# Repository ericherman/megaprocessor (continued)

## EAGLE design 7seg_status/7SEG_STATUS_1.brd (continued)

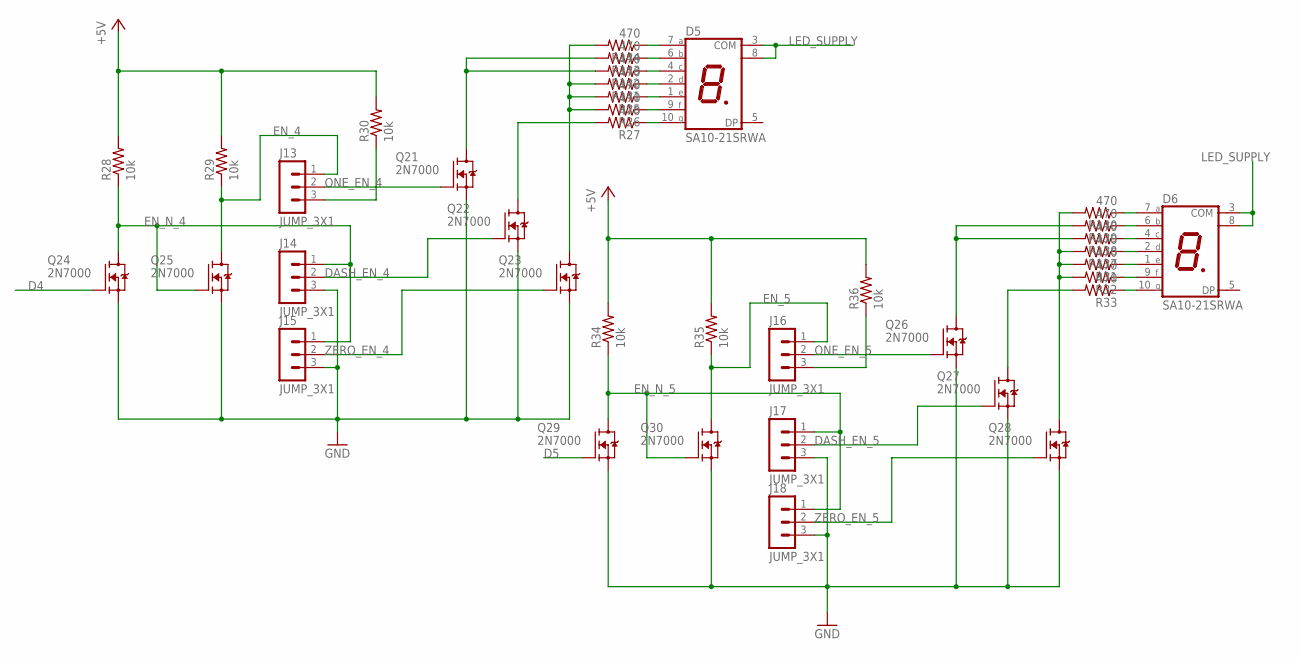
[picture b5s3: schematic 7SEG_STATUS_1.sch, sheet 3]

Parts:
D5, D6: SA10-21SRWA; SA10
J13, J14, J15, J16, J17, J18: JUMP_3X1
Q21, Q22, Q23, Q24, Q25, Q26, Q27, Q28, Q29, Q30: 2N7000; TO92-DGS
R25, R26, R27, R31, R32, R33, R137, R138, R139, R140, R141, R142, R143, R144: 470; R_P2INCH
R28, R29, R30, R34, R35, R36: 10k; R_P2INCH

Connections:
+5V: R28.2, R29.2, R30.2, R34.2, R35.2, R36.2; also elsewhere on the board
D4: Q24.G; also elsewhere on the board
D5: Q29.G; also elsewhere on the board
DASH_EN_4: J14.2, Q22.G
DASH_EN_5: J17.2, Q27.G
EN_4: J13.1, Q25.D, R29.1
EN_5: J16.1, Q30.D, R35.1
EN_N_4: J14.1, J15.1, Q24.D, Q25.G, R28.1
EN_N_5: J17.1, J18.1, Q29.D, Q30.G, R34.1
GND: J14.3, J15.3, J17.3, J18.3, Q21.S, Q22.S, Q23.S, Q24.S, Q25.S, Q26.S, Q27.S, Q28.S, Q29.S, Q30.S; also elsewhere on the board
LED_SUPPLY: D5.3 (COM), D5.8 (COM), D6.3 (COM), D6.8 (COM); also elsewhere on the board
unnamed: Q22.D, R27.2
unnamed: D6.7 (A), R140.1
unnamed: D6.6 (B), R139.1
unnamed: D6.4 (C), R138.1
unnamed: J13.3, R30.1
unnamed: D6.2 (D), R137.1
unnamed: D6.1 (E), R31.1
unnamed: D6.9 (F), R32.1
unnamed: Q21.D, R142.2, R143.2
unnamed: J16.3, R36.1
unnamed: D6.10 (G), R33.1
unnamed: Q26.D, R138.2, R139.2
unnamed: Q27.D, R33.2
unnamed: Q28.D, R31.2, R32.2, R137.2, R140.2
unnamed: Q23.D, R25.2, R26.2, R141.2, R144.2
unnamed: D5.7 (A), R144.1
unnamed: D5.6 (B), R143.1
unnamed: D5.4 (C), R142.1
unnamed: D5.2 (D), R141.1
unnamed: D5.1 (E), R25.1
unnamed: D5.9 (F), R26.1
unnamed: D5.10 (G), R27.1
ONE_EN_4: J13.2, Q21.G
ONE_EN_5: J16.2, Q26.G
ZERO_EN_4: J15.2, Q23.G
ZERO_EN_5: J18.2, Q28.G

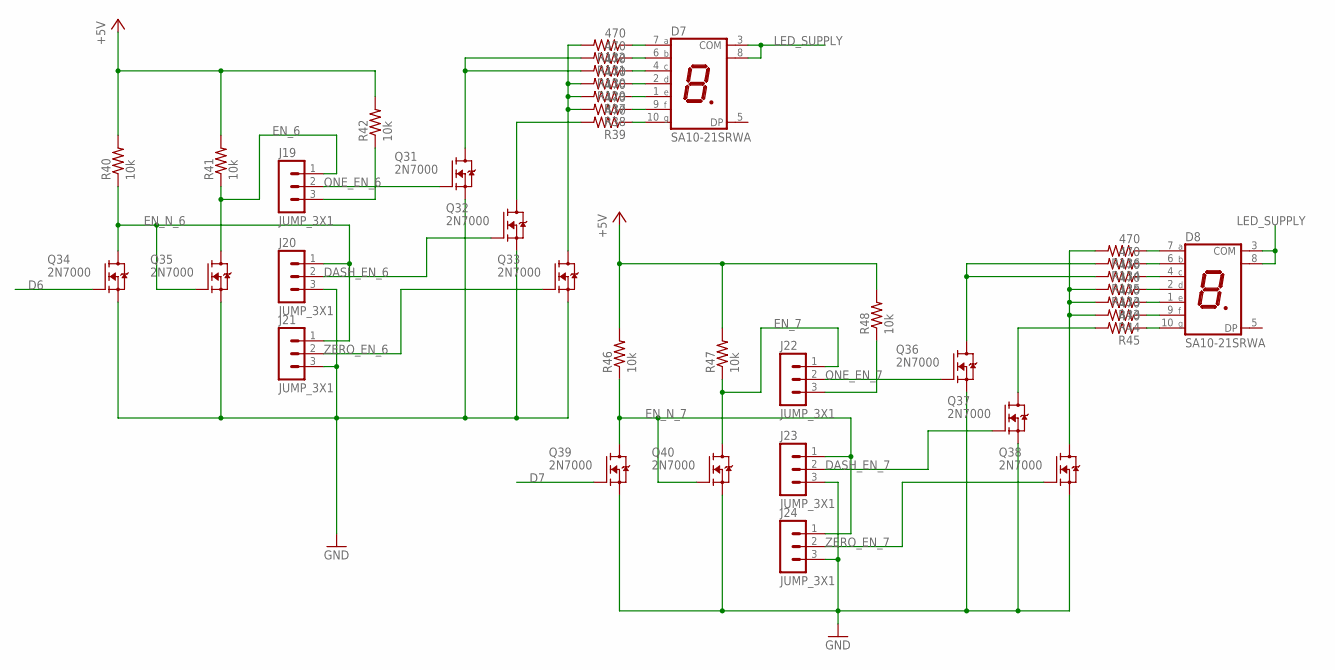
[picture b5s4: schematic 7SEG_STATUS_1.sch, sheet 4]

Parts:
D7, D8: SA10-21SRWA; SA10
J19, J20, J21, J22, J23, J24: JUMP_3X1
Q31, Q32, Q33, Q34, Q35, Q36, Q37, Q38, Q39, Q40: 2N7000; TO92-DGS
R37, R38, R39, R43, R44, R45, R129, R130, R131, R132, R133, R134, R135, R136: 470; R_P2INCH
R40, R41, R42, R46, R47, R48: 10k; R_P2INCH

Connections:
+5V: R40.2, R41.2, R42.2, R46.2, R47.2, R48.2; also elsewhere on the board
D6: Q34.G; also elsewhere on the board
D7: Q39.G; also elsewhere on the board
DASH_EN_6: J20.2, Q32.G
DASH_EN_7: J23.2, Q37.G
EN_6: J19.1, Q35.D, R41.1
EN_7: J22.1, Q40.D, R47.1
EN_N_6: J20.1, J21.1, Q34.D, Q35.G, R40.1
EN_N_7: J23.1, J24.1, Q39.D, Q40.G, R46.1
GND: J20.3, J21.3, J23.3, J24.3, Q31.S, Q32.S, Q33.S, Q34.S, Q35.S, Q36.S, Q37.S, Q38.S, Q39.S, Q40.S; also elsewhere on the board
LED_SUPPLY: D7.3 (COM), D7.8 (COM), D8.3 (COM), D8.8 (COM); also elsewhere on the board
unnamed: D7.7 (A), R132.1
unnamed: D7.6 (B), R131.1
unnamed: D7.4 (C), R130.1
unnamed: D7.2 (D), R129.1
unnamed: J19.3, R42.1
unnamed: D7.1 (E), R37.1
unnamed: D7.9 (F), R38.1
unnamed: D7.10 (G), R39.1
unnamed: D8.7 (A), R136.1
unnamed: J22.3, R48.1
unnamed: Q32.D, R39.2
unnamed: Q31.D, R130.2, R131.2
unnamed: D8.6 (B), R134.1
unnamed: D8.4 (C), R135.1
unnamed: D8.2 (D), R133.1
unnamed: D8.1 (E), R43.1
unnamed: D8.9 (F), R44.1
unnamed: D8.10 (G), R45.1
unnamed: Q37.D, R45.2
unnamed: Q36.D, R134.2, R135.2
unnamed: Q38.D, R43.2, R44.2, R133.2, R136.2
unnamed: Q33.D, R37.2, R38.2, R129.2, R132.2
ONE_EN_6: J19.2, Q31.G
ONE_EN_7: J22.2, Q36.G
ZERO_EN_6: J21.2, Q33.G
ZERO_EN_7: J24.2, Q38.G

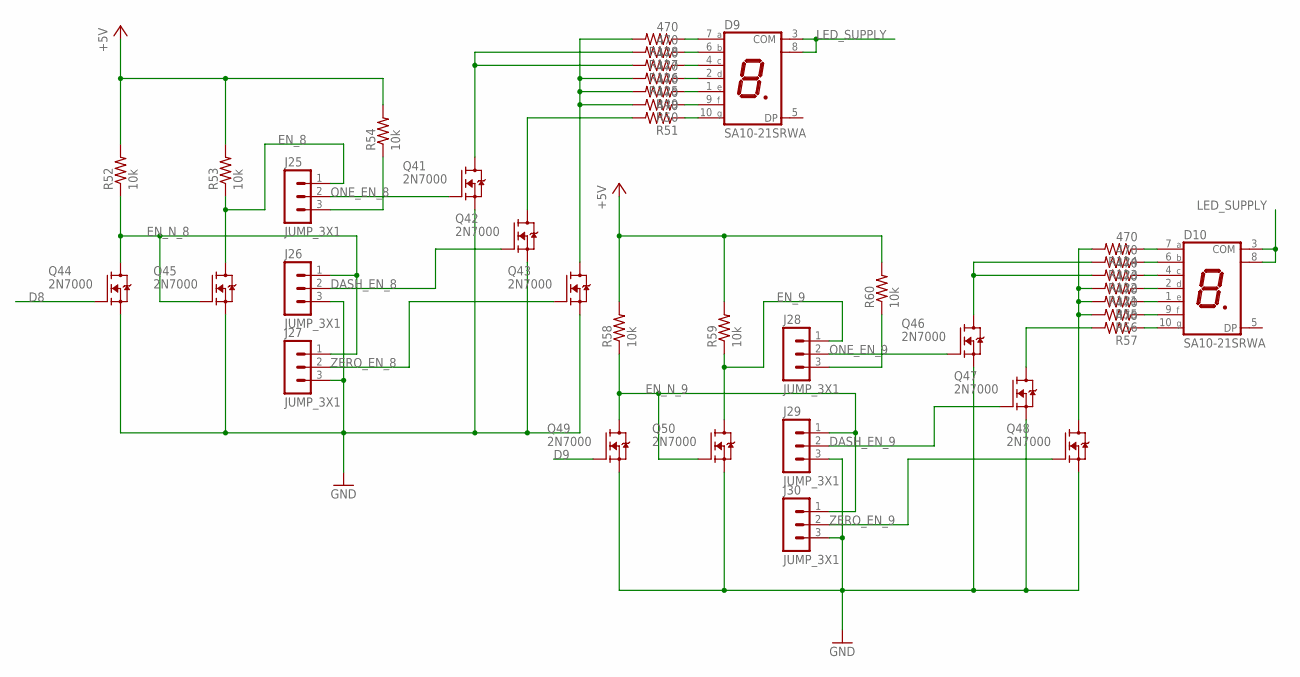
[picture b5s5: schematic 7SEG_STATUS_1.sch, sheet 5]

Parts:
D9, D10: SA10-21SRWA; SA10
J25, J26, J27, J28, J29, J30: JUMP_3X1
Q41, Q42, Q43, Q44, Q45, Q46, Q47, Q48, Q49, Q50: 2N7000; TO92-DGS
R49, R50, R51, R55, R56, R57, R121, R122, R123, R124, R125, R126, R127, R128: 470; R_P2INCH
R52, R53, R54, R58, R59, R60: 10k; R_P2INCH

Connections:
+5V: R52.2, R53.2, R54.2, R58.2, R59.2, R60.2; also elsewhere on the board
D8: Q44.G; also elsewhere on the board
D9: Q49.G; also elsewhere on the board
DASH_EN_8: J26.2, Q42.G
DASH_EN_9: J29.2, Q47.G
EN_8: J25.1, Q45.D, R53.1
EN_9: J28.1, Q50.D, R59.1
EN_N_8: J26.1, J27.1, Q44.D, Q45.G, R52.1
EN_N_9: J29.1, J30.1, Q49.D, Q50.G, R58.1
GND: J26.3, J27.3, J29.3, J30.3, Q41.S, Q42.S, Q43.S, Q44.S, Q45.S, Q46.S, Q47.S, Q48.S, Q49.S, Q50.S; also elsewhere on the board
LED_SUPPLY: D9.3 (COM), D9.8 (COM), D10.3 (COM), D10.8 (COM); also elsewhere on the board
unnamed: D9.7 (A), R128.1
unnamed: D10.10 (G), R57.1
unnamed: D10.9 (F), R56.1
unnamed: J25.3, R54.1
unnamed: D10.1 (E), R55.1
unnamed: D10.2 (D), R121.1
unnamed: D10.4 (C), R122.1
unnamed: D10.6 (B), R123.1
unnamed: J28.3, R60.1
unnamed: D10.7 (A), R124.1
unnamed: Q47.D, R57.2
unnamed: Q46.D, R122.2, R123.2
unnamed: Q48.D, R55.2, R56.2, R121.2, R124.2
unnamed: D9.6 (B), R127.1
unnamed: D9.4 (C), R126.1
unnamed: D9.2 (D), R125.1
unnamed: D9.1 (E), R49.1
unnamed: D9.9 (F), R50.1
unnamed: D9.10 (G), R51.1
unnamed: Q42.D, R51.2
unnamed: Q41.D, R126.2, R127.2
unnamed: Q43.D, R49.2, R50.2, R125.2, R128.2
ONE_EN_8: J25.2, Q41.G
ONE_EN_9: J28.2, Q46.G
ZERO_EN_8: J27.2, Q43.G
ZERO_EN_9: J30.2, Q48.G

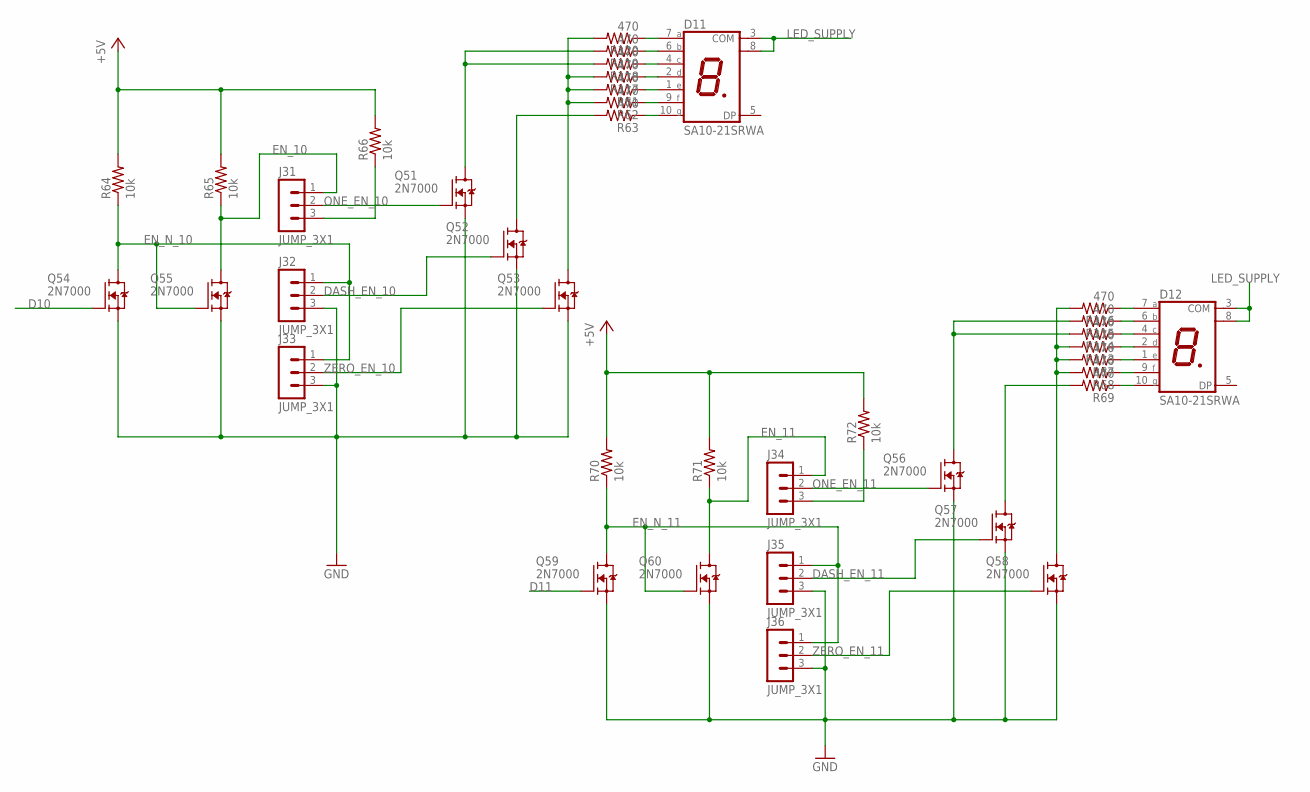
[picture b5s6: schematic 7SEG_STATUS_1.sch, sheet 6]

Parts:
D11, D12: SA10-21SRWA; SA10
J31, J32, J33, J34, J35, J36: JUMP_3X1
Q51, Q52, Q53, Q54, Q55, Q56, Q57, Q58, Q59, Q60: 2N7000; TO92-DGS
R61, R62, R63, R67, R68, R69, R113, R114, R115, R116, R117, R118, R119, R120: 470; R_P2INCH
R64, R65, R66, R70, R71, R72: 10k; R_P2INCH

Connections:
+5V: R64.2, R65.2, R66.2, R70.2, R71.2, R72.2; also elsewhere on the board
D10: Q54.G; also elsewhere on the board
D11: Q59.G; also elsewhere on the board
DASH_EN_10: J32.2, Q52.G
DASH_EN_11: J35.2, Q57.G
EN_10: J31.1, Q55.D, R65.1
EN_11: J34.1, Q60.D, R71.1
EN_N_10: J32.1, J33.1, Q54.D, Q55.G, R64.1
EN_N_11: J35.1, J36.1, Q59.D, Q60.G, R70.1
GND: J32.3, J33.3, J35.3, J36.3, Q51.S, Q52.S, Q53.S, Q54.S, Q55.S, Q56.S, Q57.S, Q58.S, Q59.S, Q60.S; also elsewhere on the board
LED_SUPPLY: D11.3 (COM), D11.8 (COM), D12.3 (COM), D12.8 (COM); also elsewhere on the board
unnamed: Q52.D, R63.2
unnamed: Q51.D, R118.2, R119.2
unnamed: D11.6 (B), R119.1
unnamed: D12.7 (A), R116.1
unnamed: J31.3, R66.1
unnamed: D12.6 (B), R115.1
unnamed: D12.4 (C), R114.1
unnamed: D12.2 (D), R113.1
unnamed: D11.4 (C), R118.1
unnamed: J34.3, R72.1
unnamed: D12.1 (E), R67.1
unnamed: D12.9 (F), R68.1
unnamed: D12.10 (G), R69.1
unnamed: Q58.D, R67.2, R68.2, R113.2, R116.2
unnamed: Q56.D, R114.2, R115.2
unnamed: Q57.D, R69.2
unnamed: D11.2 (D), R117.1
unnamed: D11.1 (E), R61.1
unnamed: D11.9 (F), R62.1
unnamed: D11.10 (G), R63.1
unnamed: D11.7 (A), R120.1
unnamed: Q53.D, R61.2, R62.2, R117.2, R120.2
ONE_EN_10: J31.2, Q51.G
ONE_EN_11: J34.2, Q56.G
ZERO_EN_10: J33.2, Q53.G
ZERO_EN_11: J36.2, Q58.G

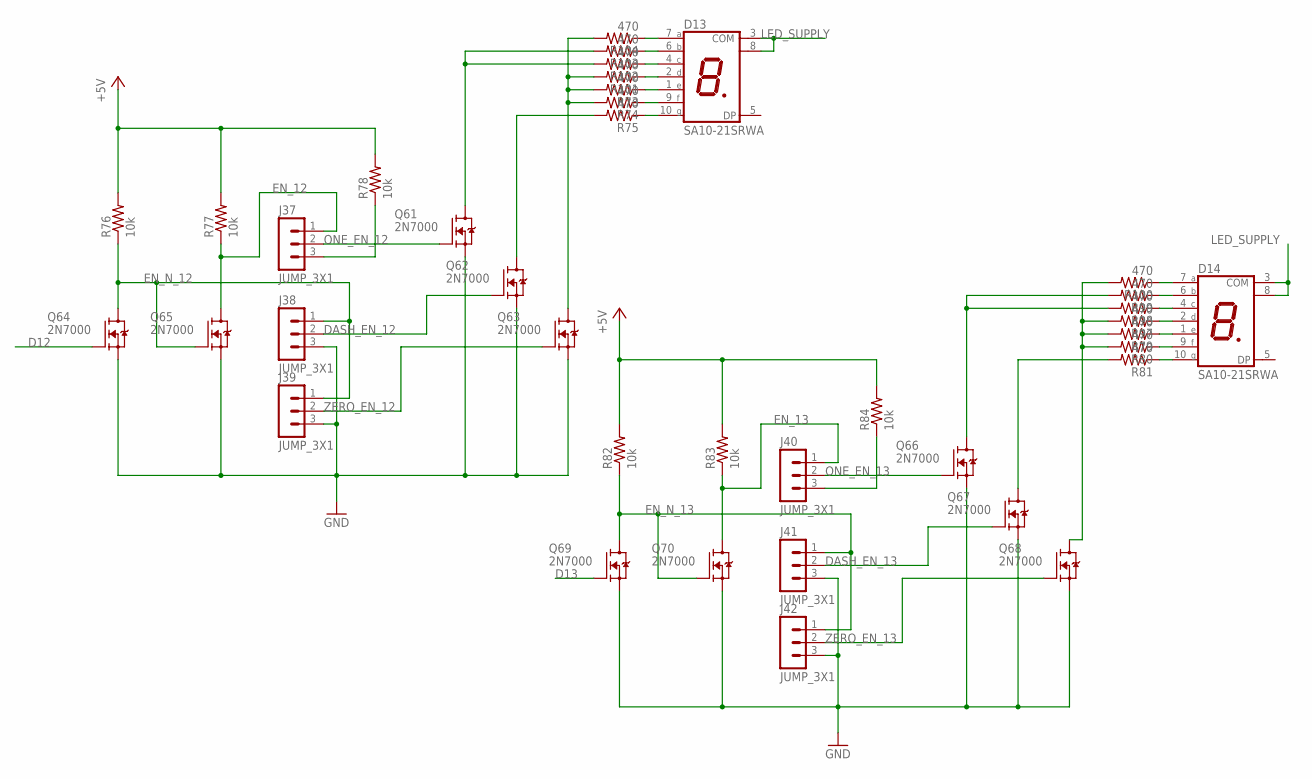
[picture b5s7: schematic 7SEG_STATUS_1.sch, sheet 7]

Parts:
D13, D14: SA10-21SRWA; SA10
J37, J38, J39, J40, J41, J42: JUMP_3X1
Q61, Q62, Q63, Q64, Q65, Q66, Q67, Q68, Q69, Q70: 2N7000; TO92-DGS
R73, R74, R75, R79, R80, R81, R97, R98, R99, R100, R101, R102, R103, R104: 470; R_P2INCH
R76, R77, R78, R82, R83, R84: 10k; R_P2INCH

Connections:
+5V: R76.2, R77.2, R78.2, R82.2, R83.2, R84.2; also elsewhere on the board
D12: Q64.G; also elsewhere on the board
D13: Q69.G; also elsewhere on the board
DASH_EN_12: J38.2, Q62.G
DASH_EN_13: J41.2, Q67.G
EN_12: J37.1, Q65.D, R77.1
EN_13: J40.1, Q70.D, R83.1
EN_N_12: J38.1, J39.1, Q64.D, Q65.G, R76.1
EN_N_13: J41.1, J42.1, Q69.D, Q70.G, R82.1
GND: J38.3, J39.3, J41.3, J42.3, Q61.S, Q62.S, Q63.S, Q64.S, Q65.S, Q66.S, Q67.S, Q68.S, Q69.S, Q70.S; also elsewhere on the board
LED_SUPPLY: D13.3 (COM), D13.8 (COM), D14.3 (COM), D14.8 (COM); also elsewhere on the board
unnamed: D13.10 (G), R75.1
unnamed: D13.9 (F), R74.1
unnamed: D13.1 (E), R73.1
unnamed: D13.2 (D), R101.1
unnamed: J37.3, R78.1
unnamed: D14.7 (A), R100.1
unnamed: D14.6 (B), R99.1
unnamed: D14.4 (C), R98.1
unnamed: D14.2 (D), R97.1
unnamed: J40.3, R84.1
unnamed: D14.1 (E), R79.1
unnamed: D14.9 (F), R80.1
unnamed: D14.10 (G), R81.1
unnamed: D13.4 (C), R102.1
unnamed: Q66.D, R98.2, R99.2
unnamed: D13.6 (B), R103.1
unnamed: Q67.D, R81.2
unnamed: Q68.D, R79.2, R80.2, R97.2, R100.2
unnamed: D13.7 (A), R104.1
unnamed: Q62.D, R75.2
unnamed: Q61.D, R102.2, R103.2
unnamed: Q63.D, R73.2, R74.2, R101.2, R104.2
ONE_EN_12: J37.2, Q61.G
ONE_EN_13: J40.2, Q66.G
ZERO_EN_12: J39.2, Q63.G
ZERO_EN_13: J42.2, Q68.G

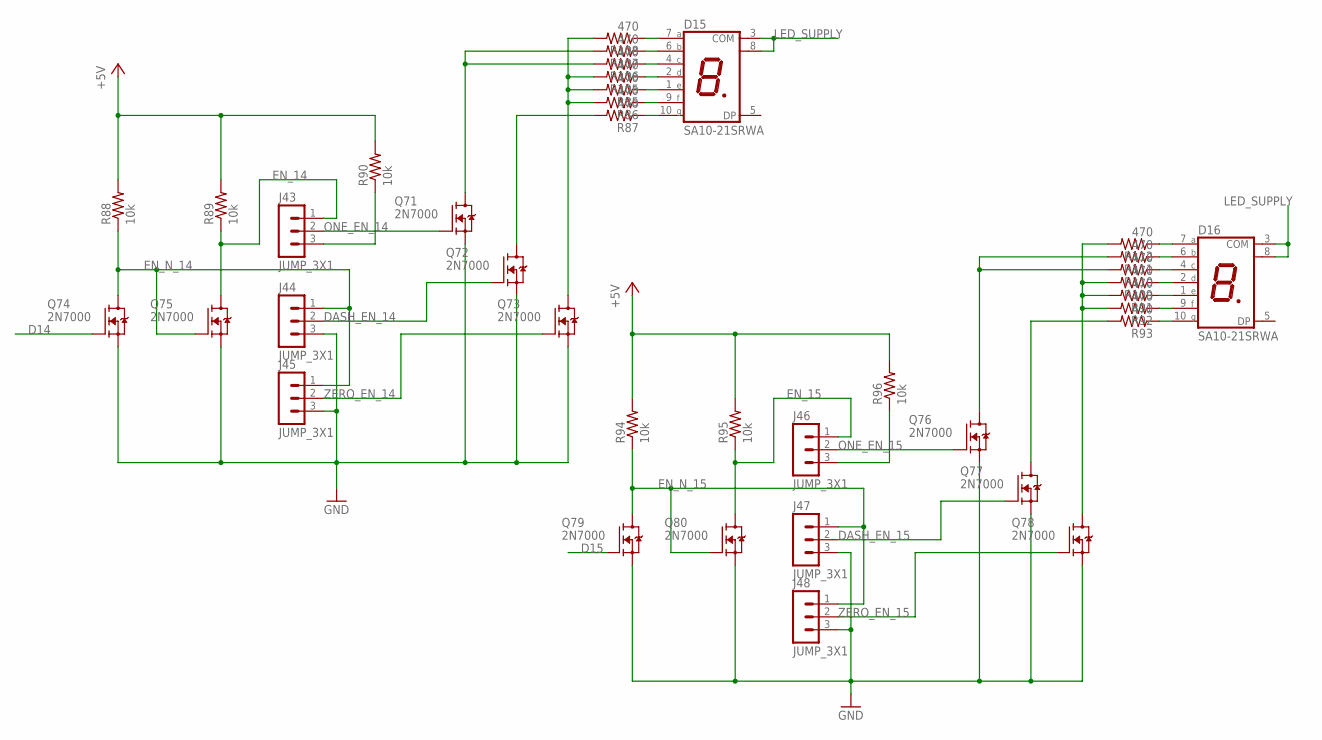
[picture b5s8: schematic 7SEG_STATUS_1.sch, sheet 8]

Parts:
D15, D16: SA10-21SRWA; SA10
J43, J44, J45, J46, J47, J48: JUMP_3X1
Q71, Q72, Q73, Q74, Q75, Q76, Q77, Q78, Q79, Q80: 2N7000; TO92-DGS
R85, R86, R87, R91, R92, R93, R105, R106, R107, R108, R109, R110, R111, R112: 470; R_P2INCH
R88, R89, R90, R94, R95, R96: 10k; R_P2INCH

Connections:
+5V: R88.2, R89.2, R90.2, R94.2, R95.2, R96.2; also elsewhere on the board
D14: Q74.G; also elsewhere on the board
D15: Q79.G; also elsewhere on the board
DASH_EN_14: J44.2, Q72.G
DASH_EN_15: J47.2, Q77.G
EN_14: J43.1, Q75.D, R89.1
EN_15: J46.1, Q80.D, R95.1
EN_N_14: J44.1, J45.1, Q74.D, Q75.G, R88.1
EN_N_15: J47.1, J48.1, Q79.D, Q80.G, R94.1
GND: J44.3, J45.3, J47.3, J48.3, Q71.S, Q72.S, Q73.S, Q74.S, Q75.S, Q76.S, Q77.S, Q78.S, Q79.S, Q80.S; also elsewhere on the board
LED_SUPPLY: D15.3 (COM), D15.8 (COM), D16.3 (COM), D16.8 (COM); also elsewhere on the board
unnamed: D15.10 (G), R87.1
unnamed: D15.9 (F), R86.1
unnamed: D15.1 (E), R85.1
unnamed: J43.3, R90.1
unnamed: D16.10 (G), R93.1
unnamed: D16.9 (F), R92.1
unnamed: D16.1 (E), R91.1
unnamed: D16.2 (D), R109.1
unnamed: J46.3, R96.1
unnamed: D16.4 (C), R110.1
unnamed: D16.6 (B), R111.1
unnamed: D15.2 (D), R105.1
unnamed: D15.4 (C), R106.1
unnamed: D15.6 (B), R107.1
unnamed: D15.7 (A), R108.1
unnamed: Q72.D, R87.2
unnamed: Q71.D, R106.2, R107.2
unnamed: Q73.D, R85.2, R86.2, R105.2, R108.2
unnamed: D16.7 (A), R112.1
unnamed: Q77.D, R93.2
unnamed: Q76.D, R110.2, R111.2
unnamed: Q78.D, R91.2, R92.2, R109.2, R112.2
ONE_EN_14: J43.2, Q71.G
ONE_EN_15: J46.2, Q76.G
ZERO_EN_14: J45.2, Q73.G
ZERO_EN_15: J48.2, Q78.G

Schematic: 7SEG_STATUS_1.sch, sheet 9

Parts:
C1, C2: 100u; POLARISED_CAP_2P5_6P3MM
C3, C4: 100n; CAP_P2INCH
HOLE1, HOLE2, HOLE3, HOLE4, HOLE5, HOLE6: 3M_MOUNT_HOLE; 3M_HOLE
J49: 30_HDR_LOCKING_RA
PP1, PP2, PP3: POWER_PAD

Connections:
+5V: C1.A, C3.1, PP2.1; also elsewhere on the board
D0: J49.2; also elsewhere on the board
D1: J49.3; also elsewhere on the board
D2: J49.4; also elsewhere on the board
D3: J49.5; also elsewhere on the board
D4: J49.6; also elsewhere on the board
D5: J49.7; also elsewhere on the board
D6: J49.8; also elsewhere on the board
D7: J49.9; also elsewhere on the board
D8: J49.12; also elsewhere on the board
D9: J49.13; also elsewhere on the board
D10: J49.14; also elsewhere on the board
D11: J49.15; also elsewhere on the board
D12: J49.16; also elsewhere on the board
D13: J49.17; also elsewhere on the board
D14: J49.18; also elsewhere on the board
D15: J49.19; also elsewhere on the board
GND: C1.K, C2.K, C3.2, C4.2, J49.1, J49.10, J49.11, J49.20, J49.21, J49.30, PP1.1; also elsewhere on the board
LED_SUPPLY: C2.A, C4.1, PP3.1; also elsewhere on the board

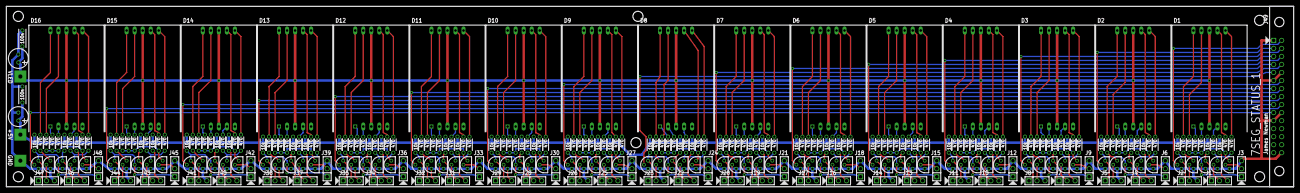
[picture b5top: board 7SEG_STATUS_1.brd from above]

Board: 2 copper layers, 407.7 x 57.1 mm, 318 parts (0 on the bottom side), 275 nets.

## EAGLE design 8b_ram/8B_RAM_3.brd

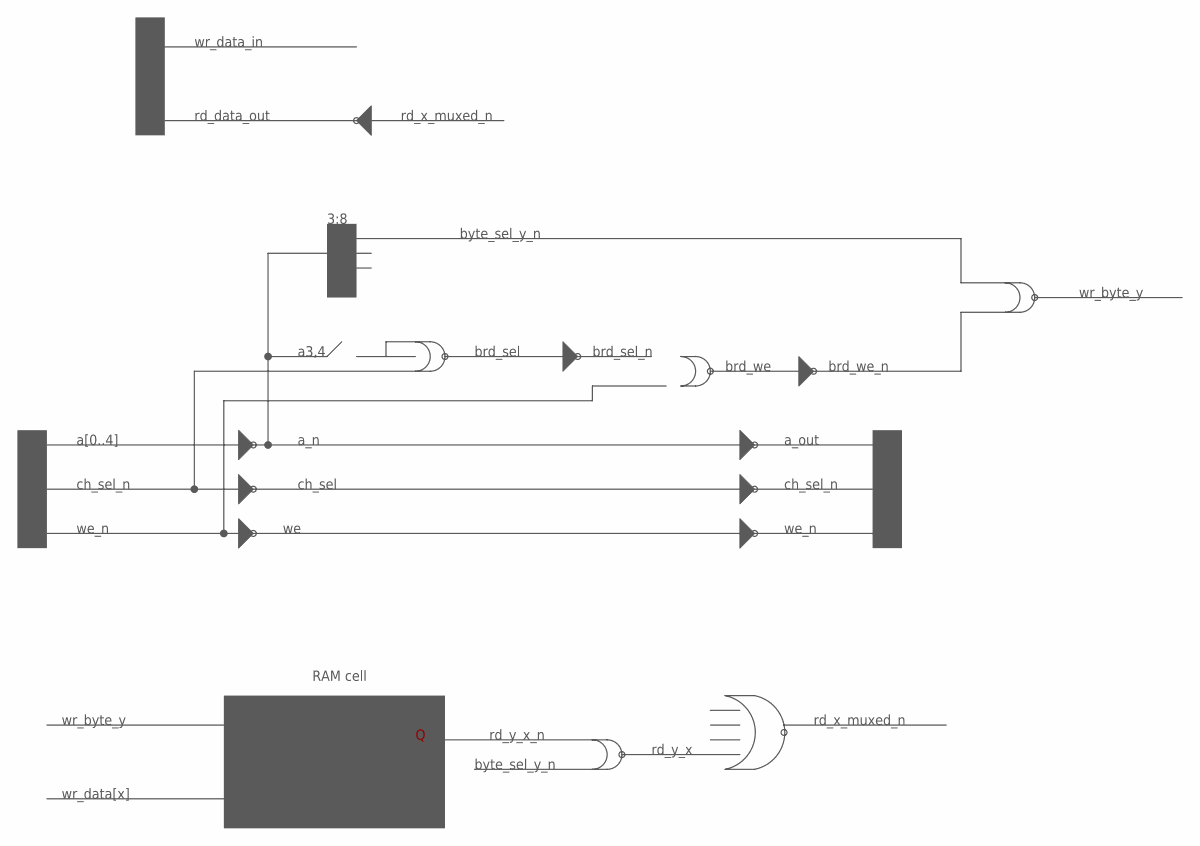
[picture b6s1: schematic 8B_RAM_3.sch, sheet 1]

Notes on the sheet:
a[0..4]
ch_sel_n
we_n
a_n
ch_sel
a_out
wr_data_in
rd_data_out
rd_x_muxed_n
3:8
a3,4
byte_sel_y_n
brd_sel
brd_sel_n
brd_we
brd_we_n
wr_byte_y
RAM cells
RAM cell
wr_data[x]
rd_y_x_n
rd_y_x

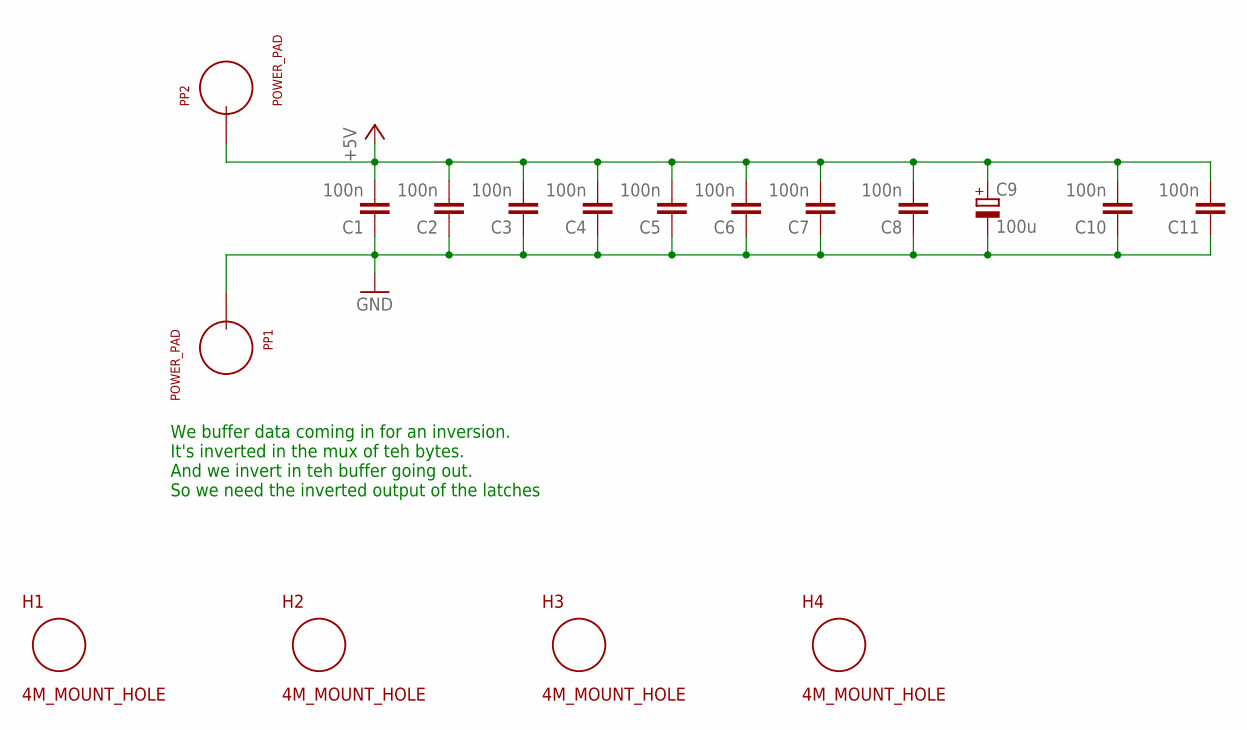
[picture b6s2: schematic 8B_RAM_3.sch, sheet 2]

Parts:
C1, C2, C3, C4, C5, C6, C7, C8, C10, C11: 100n; CAP_P2INCH
C9: 100u; POLARISED_CAP_2P5_6P3MM
H1, H2, H3, H4: 4M_MOUNT_HOLE; 4M_HOLE
PP1, PP2: POWER_PAD

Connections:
+5V: C1.2, C2.2, C3.2, C4.2, C5.2, C6.2, C7.2, C8.2, C9.A, C10.2, C11.2, PP2.1; also elsewhere on the board
GND: C1.1, C2.1, C3.1, C4.1, C5.1, C6.1, C7.1, C8.1, C9.K, C10.1, C11.1, PP1.1; also elsewhere on the board

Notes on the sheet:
We buffer data coming in for an inversion. It's inverted in the mux of teh bytes. And we invert in teh buffer going out. So we need the inverted output of the latches

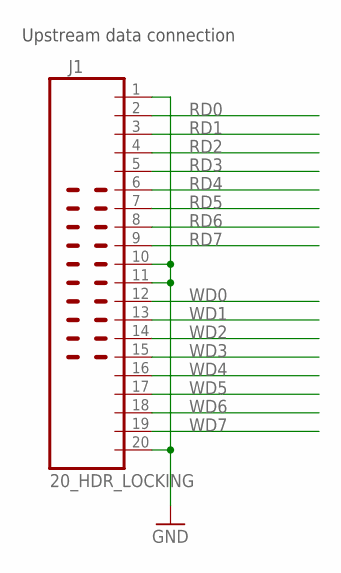
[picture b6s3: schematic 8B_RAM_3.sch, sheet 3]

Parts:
J1: 20_HDR_LOCKING

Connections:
GND: J1.1, J1.10, J1.11, J1.20; also elsewhere on the board
RD0: J1.2; also elsewhere on the board
RD1: J1.3; also elsewhere on the board
RD2: J1.4; also elsewhere on the board
RD3: J1.5; also elsewhere on the board
RD4: J1.6; also elsewhere on the board
RD5: J1.7; also elsewhere on the board
RD6: J1.8; also elsewhere on the board
RD7: J1.9; also elsewhere on the board
WD0: J1.12; also elsewhere on the board
WD1: J1.13; also elsewhere on the board
WD2: J1.14; also elsewhere on the board
WD3: J1.15; also elsewhere on the board
WD4: J1.16; also elsewhere on the board
WD5: J1.17; also elsewhere on the board
WD6: J1.18; also elsewhere on the board
WD7: J1.19; also elsewhere on the board

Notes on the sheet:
Upstream data connection

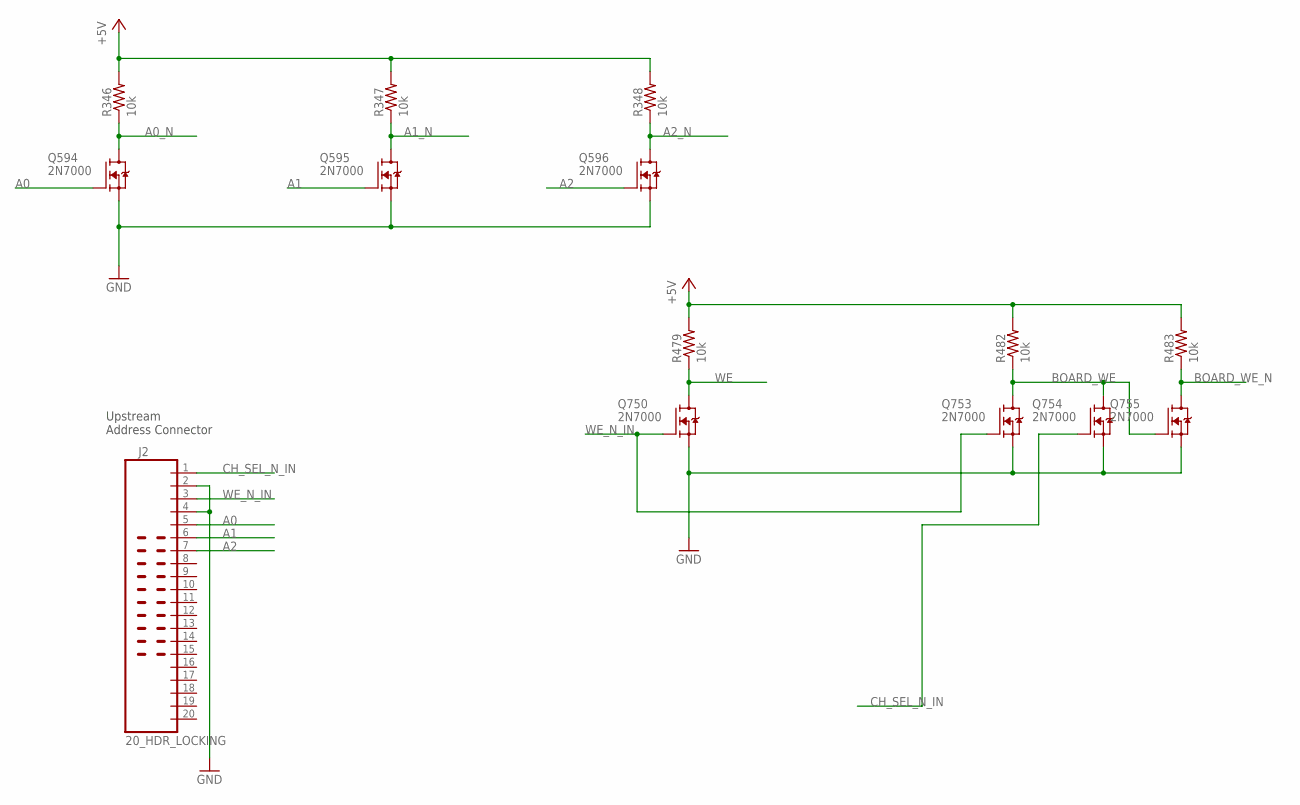
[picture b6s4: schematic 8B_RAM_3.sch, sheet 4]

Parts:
J2: 20_HDR_LOCKING
Q594, Q595, Q596, Q750, Q753, Q754, Q755: 2N7000; TO92-DGS
R346, R347, R348, R479, R482, R483: 10k; R_P2INCH

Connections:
+5V: R346.2, R347.2, R348.2, R479.2, R482.2, R483.2; also elsewhere on the board
A0: J2.5, Q594.G; also elsewhere on the board
A0_N: Q594.D, R346.1; also elsewhere on the board
A1: J2.6, Q595.G; also elsewhere on the board
A1_N: Q595.D, R347.1; also elsewhere on the board
A2: J2.7, Q596.G; also elsewhere on the board
A2_N: Q596.D, R348.1; also elsewhere on the board
BOARD_WE: Q753.D, Q754.D, Q755.G, R482.1
BOARD_WE_N: Q755.D, R483.1; also elsewhere on the board
CH_SEL_N_IN: J2.1, Q754.G
GND: J2.2, J2.4, Q594.S, Q595.S, Q596.S, Q750.S, Q753.S, Q754.S, Q755.S; also elsewhere on the board
WE: Q750.D, R479.1
WE_N_IN: J2.3, Q750.G, Q753.G

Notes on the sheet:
Upstream Address Connector

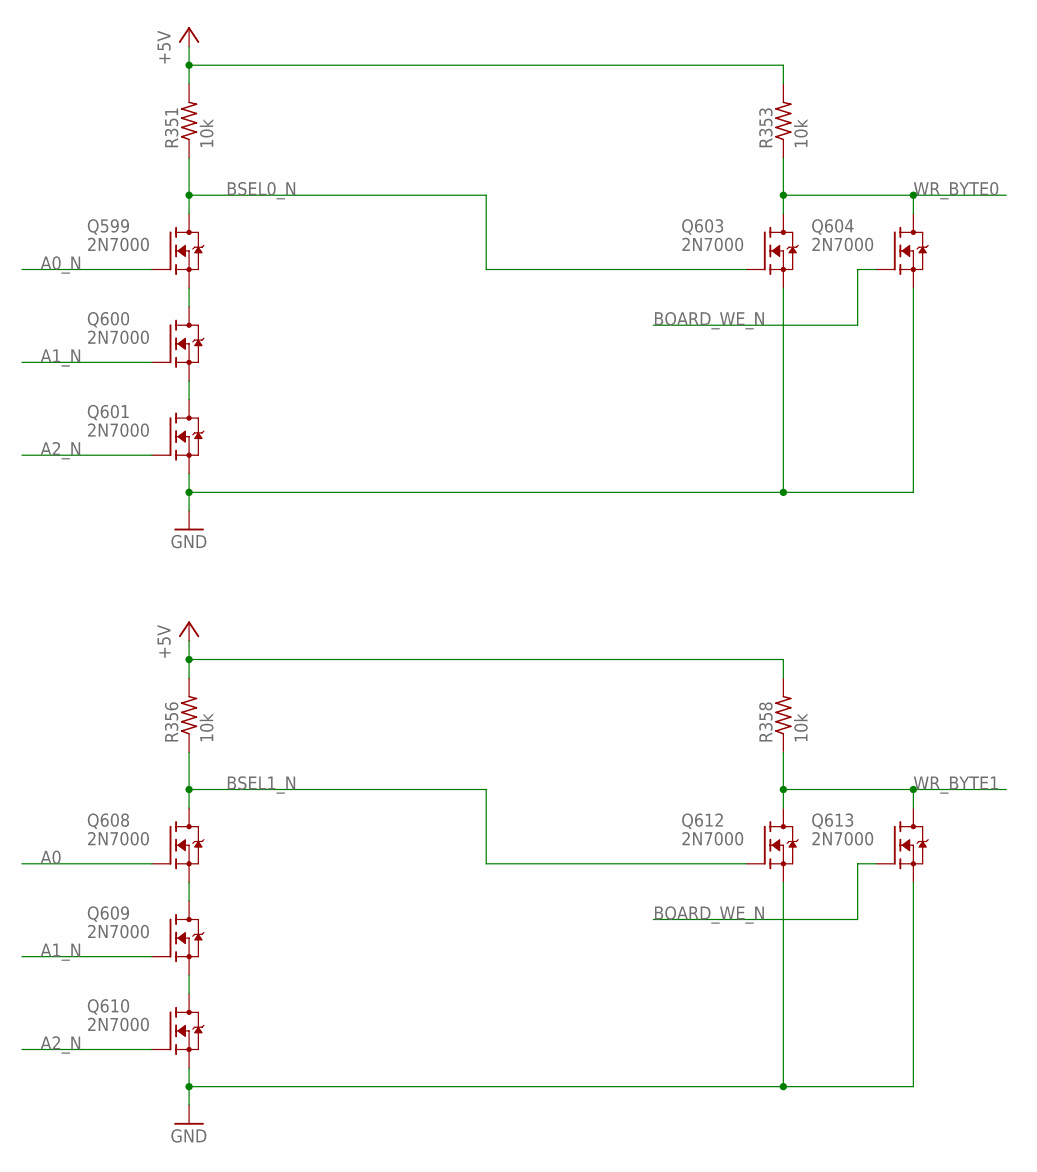
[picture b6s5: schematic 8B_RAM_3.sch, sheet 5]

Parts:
Q599, Q600, Q601, Q603, Q604, Q608, Q609, Q610, Q612, Q613: 2N7000; TO92-DGS
R351, R353, R356, R358: 10k; R_P2INCH

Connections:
+5V: R351.2, R353.2, R356.2, R358.2; also elsewhere on the board
A0: Q608.G; also elsewhere on the board
A0_N: Q599.G; also elsewhere on the board
A1_N: Q600.G, Q609.G; also elsewhere on the board
A2_N: Q601.G, Q610.G; also elsewhere on the board
BOARD_WE_N: Q604.G, Q613.G; also elsewhere on the board
BSEL0_N: Q599.D, Q603.G, R351.1; also elsewhere on the board
BSEL1_N: Q608.D, Q612.G, R356.1; also elsewhere on the board
GND: Q601.S, Q603.S, Q604.S, Q610.S, Q612.S, Q613.S; also elsewhere on the board
unnamed: Q608.S, Q609.D
unnamed: Q599.S, Q600.D
unnamed: Q600.S, Q601.D
unnamed: Q609.S, Q610.D
WR_BYTE0: Q603.D, Q604.D, R353.1; also elsewhere on the board
WR_BYTE1: Q612.D, Q613.D, R358.1; also elsewhere on the board

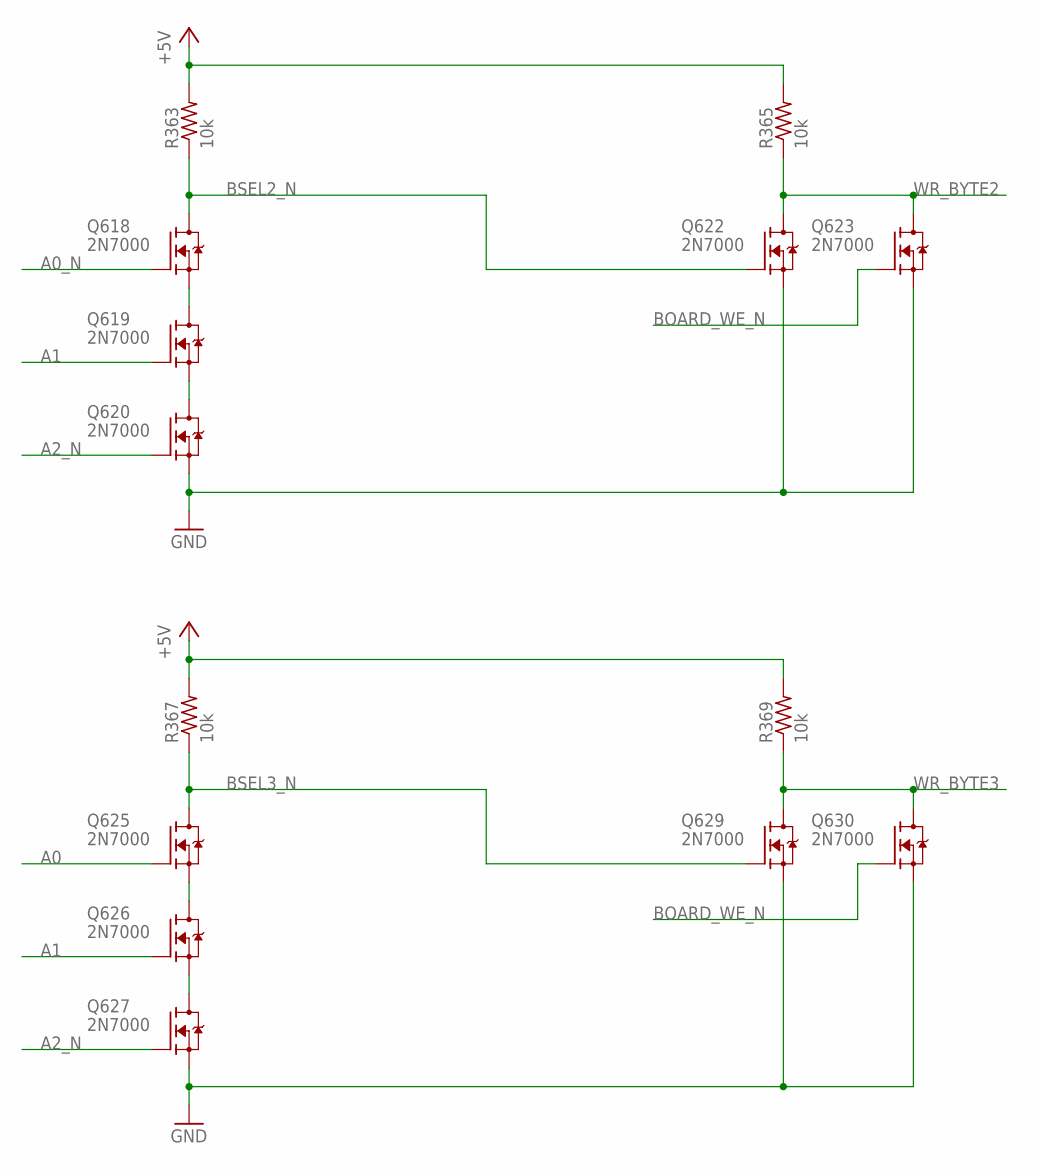
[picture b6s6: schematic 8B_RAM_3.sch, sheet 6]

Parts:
Q618, Q619, Q620, Q622, Q623, Q625, Q626, Q627, Q629, Q630: 2N7000; TO92-DGS
R363, R365, R367, R369: 10k; R_P2INCH

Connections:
+5V: R363.2, R365.2, R367.2, R369.2; also elsewhere on the board
A0: Q625.G; also elsewhere on the board
A0_N: Q618.G; also elsewhere on the board
A1: Q619.G, Q626.G; also elsewhere on the board
A2_N: Q620.G, Q627.G; also elsewhere on the board
BOARD_WE_N: Q623.G, Q630.G; also elsewhere on the board
BSEL2_N: Q618.D, Q622.G, R363.1; also elsewhere on the board
BSEL3_N: Q625.D, Q629.G, R367.1; also elsewhere on the board
GND: Q620.S, Q622.S, Q623.S, Q627.S, Q629.S, Q630.S; also elsewhere on the board
unnamed: Q618.S, Q619.D
unnamed: Q619.S, Q620.D
unnamed: Q625.S, Q626.D
unnamed: Q626.S, Q627.D
WR_BYTE2: Q622.D, Q623.D, R365.1; also elsewhere on the board
WR_BYTE3: Q629.D, Q630.D, R369.1; also elsewhere on the board

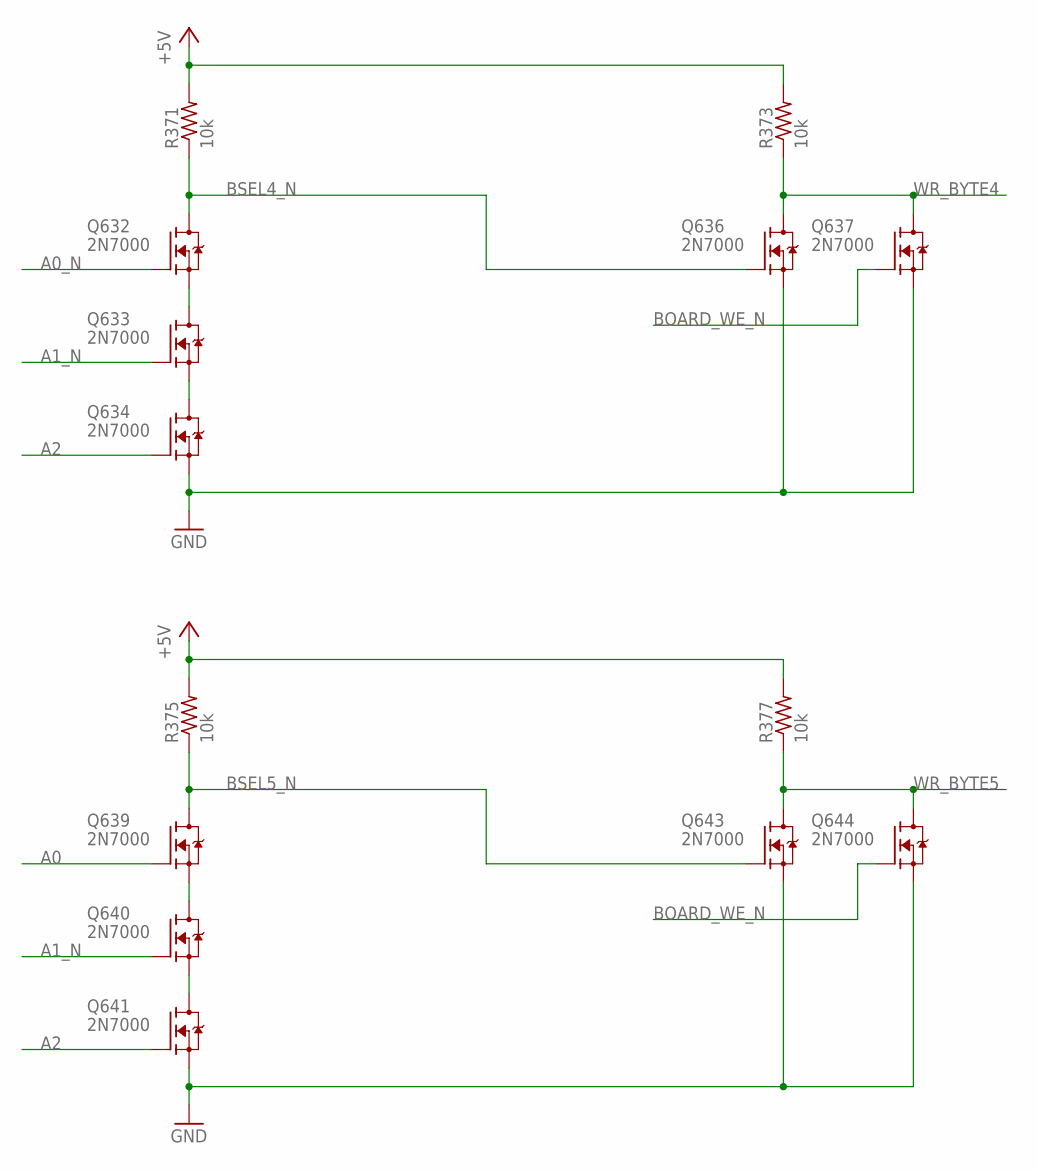
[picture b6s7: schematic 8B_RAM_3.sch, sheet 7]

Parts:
Q632, Q633, Q634, Q636, Q637, Q639, Q640, Q641, Q643, Q644: 2N7000; TO92-DGS
R371, R373, R375, R377: 10k; R_P2INCH

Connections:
+5V: R371.2, R373.2, R375.2, R377.2; also elsewhere on the board
A0: Q639.G; also elsewhere on the board
A0_N: Q632.G; also elsewhere on the board
A1_N: Q633.G, Q640.G; also elsewhere on the board
A2: Q634.G, Q641.G; also elsewhere on the board
BOARD_WE_N: Q637.G, Q644.G; also elsewhere on the board
BSEL4_N: Q632.D, Q636.G, R371.1; also elsewhere on the board
BSEL5_N: Q639.D, Q643.G, R375.1; also elsewhere on the board
GND: Q634.S, Q636.S, Q637.S, Q641.S, Q643.S, Q644.S; also elsewhere on the board
unnamed: Q632.S, Q633.D
unnamed: Q633.S, Q634.D
unnamed: Q639.S, Q640.D
unnamed: Q640.S, Q641.D
WR_BYTE4: Q636.D, Q637.D, R373.1; also elsewhere on the board
WR_BYTE5: Q643.D, Q644.D, R377.1; also elsewhere on the board
